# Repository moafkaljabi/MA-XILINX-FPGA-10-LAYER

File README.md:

# MA-XILINX

                                Front

                                Back

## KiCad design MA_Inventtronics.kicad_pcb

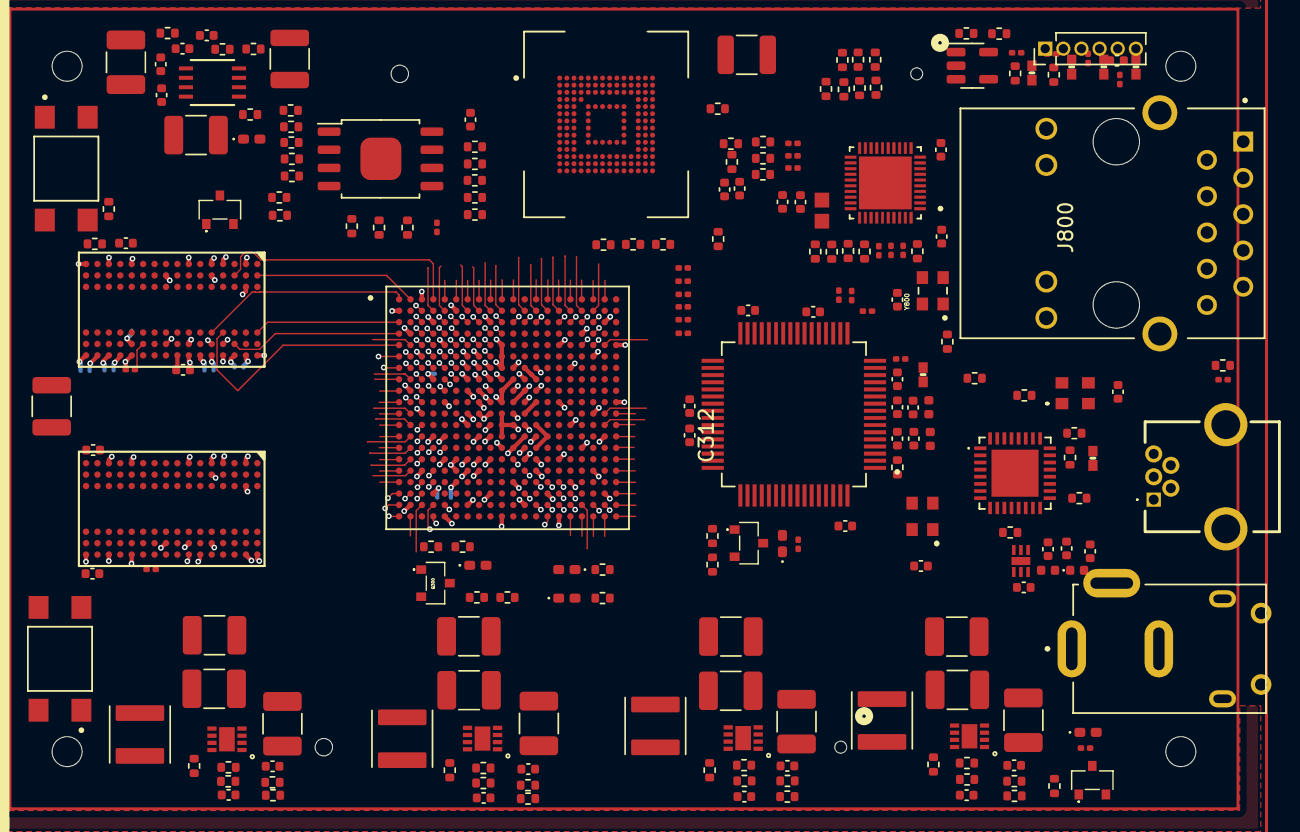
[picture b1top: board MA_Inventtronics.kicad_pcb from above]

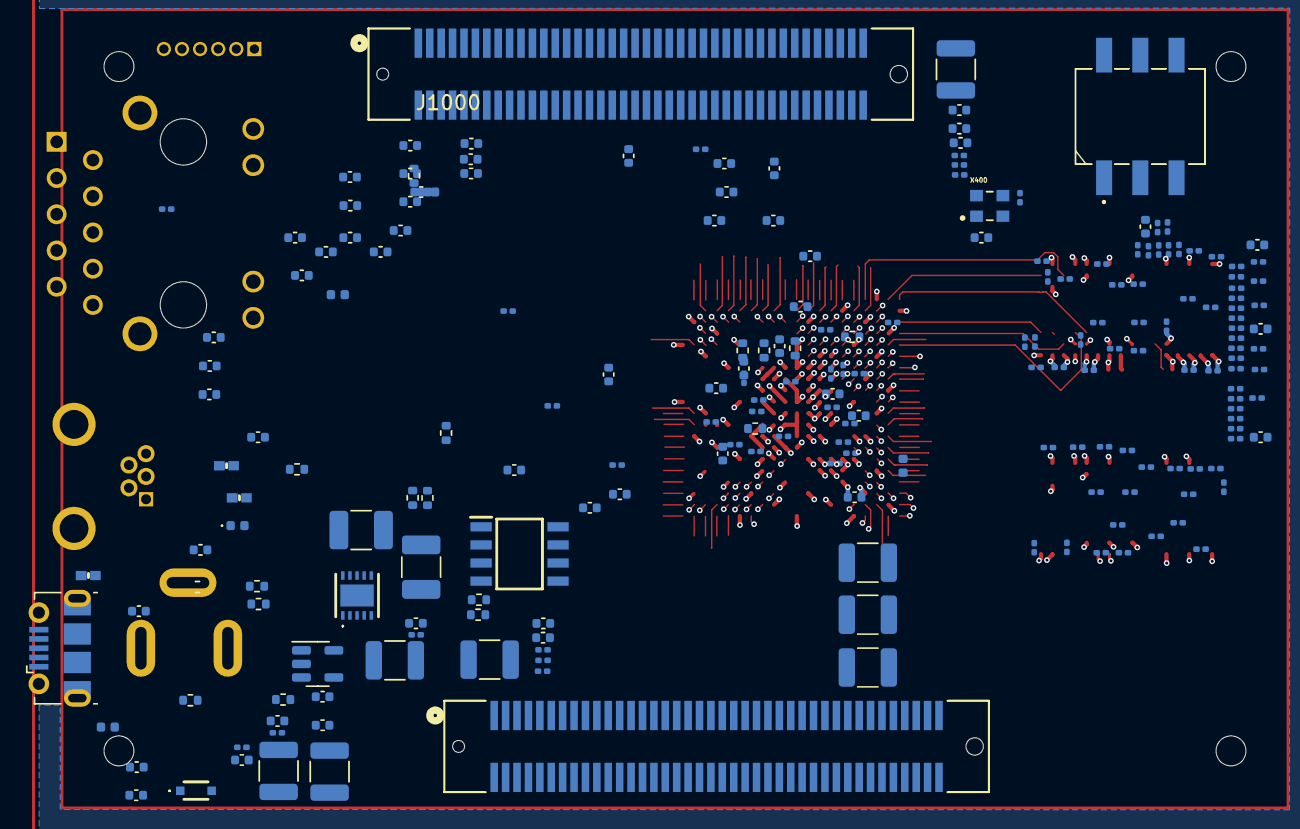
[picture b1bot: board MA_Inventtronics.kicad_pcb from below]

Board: 10 copper layers, 429 parts (207 on the bottom side), 351 nets.

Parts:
C100, C103, C104, C107, C108, C109, C112, C113, C114, C117, C118, C119, C122, C123, C124, C127: 22u; C_1210_3225Metric_Pad1.33x2.70mm_HandSolder
C101, C102, C105, C110, C115, C120, C300, C304, C306, C307, C308, C309, C310, C311, C312, C313, C314, C316, C318, C400, C401, C402, C403, C404, C405, C406, C407, C409, C412, C801, C802, C803, C804, C805, C806, C807, C808, C810, C811, C813, C815, C817, C818, C900, C901, C902, C903, C904, C905, C906, C908: 100n; C_0402_1005Metric
C106, C111, C116, C121: 22p; C_0402_1005Metric
C125, C126, C128, C129, C201, C205, C210, C213, C216, C220, C223, C229, C232, C237, C239, C244, C246, C301, C302, C303, C305, C315, C408, C410, C411, C413, C608, C609, C610, C611, C702, C712, C724, C734, C800, C809, C812, C814, C816, C819, C907: 4u7; C_0402_1005Metric
C130: 1n; C_0201_0603Metric
C200, C204, C209, C212, C221, C224, C230, C233, C234, C235, C248: 100u; C_1210_3225Metric
C202, C203, C206, C207, C208, C211, C214, C215, C217, C218, C219, C222, C225, C226, C228, C231, C238, C240, C241, C242, C243, C245, C247, C604, C605, C606, C607, C703, C713, C725, C735: 470n; C_0201_0603Metric
C227, C236: 470n; C_0402_1005Metric
C600, C601, C602, C603, C612, C613, C700, C701, C704, C705, C706, C707, C708, C709, C710, C711, C714, C715, C716, C717, C718, C719, C720, C721, C722, C723, C726, C727, C728, C729, C730, C731, C732, C733, C736, C737, C738, C739, C740, C741, C742, C743: 47n; C_0201_0603Metric
D100: PMEG1030EJ; PMEG1030EJ115
D101: LED; LED_0402_1005Metric_Pad0.77x0.64mm_HandSolder
D300, D308, D309: LED_G; LED_0402_1005Metric_Pad0.77x0.64mm_HandSolder
D301, D302, D303, D304, D306, D307, D900, D901, D902: CG0402MLU-3.3G; VARC1005X41N
D305, D903: PMEG1030EJ; D_0402_1005Metric
D400: D400; LED_0402_1005Metric_Pad0.77x0.64mm_HandSolder
D500: GREEN; LED_0402_1005Metric_Pad0.77x0.64mm_HandSolder
FB200, FB300, FB301, FB302, FB800, FB801, FB900: 120R; L_0402_1005Metric
H901, H902, H903, H904: MountingHole; MountingHole_2.1mm
J100: Barrel_Jack_Switch; GRAVITECH_CON-SOCJ-2155
J302: USB_B_Micro; USB_Micro-B_Molex-105017-0001
J304: PinHeader_1x06_P1.27mm_Vertical
J800: HR911130A; HANRUN_HR911130A
J900: GMSB0522132EU
J1000, J1001: 10144518-082802LF; CONN_10144518_AMP
L100, L101, L102, L103: 2u2; L_Abracon_ASPI-4030S
L800: LQM18PN3R3MGHD; INDC1608X100N
Q100, Q300, Q400, Q500: T2N7002AK,LM; TBAT54CLM
R100, R104, R109, R114, R119, R126, R401: 100k; R_0402_1005Metric
R101, R103, R105, R108, R110, R113, R115, R118, R120, R123, R125: 12k; R_0402_1005Metric
R102, R300, R301, R302, R303, R304: 4k7; R_0402_1005Metric
R106, R421, R422, R423, R424, R425: 68K; R_0402_1005Metric
R107, R112, R117, R122, R322, R323, R414, R416, R501: 100K; R_0402_1005Metric
R111: 200K; R_0402_1005Metric
R116: 124K; R_0402_1005Metric
R121: 453K; R_0402_1005Metric
R124, R503, R823: 510R; R_0201_0603Metric
R127, R311, R313, R315, R500, R803, R805, R806, R813, R814: 1K; R_0402_1005Metric
R128: DNP_1M; R_0402_1005Metric
R305, R306, R307, R308, R329, R330, R331, R332, R333, R334, R335, R406, R407, R408, R409, R410, R411, R419, R420, R427, R807, R811, R812, R815, R816, R817: 22R; R_0201_0603Metric
R309, R336, R337, R412, R822: 510R; R_0402_1005Metric
R310, R312, R314, R316, R318, R319, R321, R338, R404, R405: 20K; R_0402_1005Metric
R317, R320, R428: DNP_0R; R_0402_1005Metric
R324, R326, R327, R328, R400, R402, R403, R413, R417, R418, R426, R502, R903: 12K; R_0402_1005Metric
R325, R821: 2K49; R_0402_1005Metric
R600, R626, R627: 100R; R_0201_0603Metric
R601, R602, R603, R604, R605, R606, R607, R608, R609, R610, R611, R612, R613, R614, R615, R616, R617, R618, R619, R620, R621, R622, R623, R624: 49R9; R_0201_0603Metric
R625, R800, R801, R804, R818, R819, R820, R904, R905: 4K7; R_0402_1005Metric
R700, R701: 240R; R_0201_0603Metric
R802: DNP_4K7; R_0402_1005Metric
R808, R809, R810, R901: 22R; R_0402_1005Metric
R900: 1k; R_0402_1005Metric
R902: 8K06; R_0402_1005Metric
SW300, SW400: TL3305BF160QG; SW_TL3305BF160QG
SW301: 219-3LPST; 2193LPST
U100: LS1205EVD33
U101, U102, U103, U104: SY8003ADFC; SON50P200X200X65-9N
U105: BD3539FVM-TR; MSOP8_ROM
U200: XC7Z007S-1CLG400C; BGA400C80P20X20_1700X1700X160N
U300: FT2232HL-REEL; QFP50P1200X1200X160-64N
U301: 93LC56B-I_SN; SOIC127P600X175-8N
U400, U401: SN74LVC1G14DBV; SOT-23-5
U403: S40FC004C1B1I00000; BGA153N50P14X14_1150X1300X80
U404: W25Q128JVEIQ; SOIC-8_5.23x5.23mm_P1.27mm
U700, U701: MT41K256M16TW-107_P; TFBGA-96
U800: RTL8211F-CG; QFN40P500X500X90-41N
U900: USB3320C-EZK-TR; QFN50P500X500X100-33N330X330
U901: MIC2099-1YMT-TR; TMLF-6_MT_MCH
X300: ECS-2520MV-120-BN-TR; ECS2520MV120BNTR
X400: ECS-2520MV-333.3-BN-TR; OSC_ECS-2520S25-250-FN-TR
Y800: ECS-2520MV-250-BN-TR; OSC_ECS-2520S25-250-FN-TR
Y900: ECS-2520MV-130-BN-TR; ECS2520MV130BNTR

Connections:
+5V: C104.1, C109.1, C114.1, C119.1, R103.1, R105.1, R108.1, R113.1, R118.1, U101.3 (IN), U102.3 (IN), U103.3 (IN), U104.3 (IN)
/1. Power/DDR_VTT_EN: C125.1, R125.2, R126.1, R127.2, U105.2 (EN), U105.5 (VDDQ)
/1. Power/EN_1V0: R105.2, R110.2, R115.2, R120.2, U101.7 (EN), U102.7 (EN), U103.7 (EN), U104.7 (EN)
/1. Power/FB 1V0: C106.2, C111.2, C116.2, C121.2, R106.2, R107.1, R111.2, R112.1, R116.2, R117.1, R121.2, R122.1, U101.1 (FB), U102.1 (FB), U103.1 (FB), U104.1 (FB)
/1. Power/LED_PWR_A: D101.2 (A), R124.2
/1. Power/LED_PWR_C: D101.1 (K), Q100.2 (S)
/1. Power/PG_1V0: C105.1, C110.1, C115.1, C120.1, R103.2, R104.1, R108.2, R109.1, R113.2, R114.1, R118.2, R119.1, R123.2, U101.2 (PG), U102.2 (PG), U103.2 (PG), U104.2 (PG)
/1. Power/PWR_EN: C101.1, R100.2, U100.7 (EN)
/1. Power/SW_1V0: L100.1, L101.1, L102.1, L103.1, U101.6 (LX), U102.6 (LX), U103.6 (LX), U104.6 (LX)
/1. Power/eFuse_ILIM: R102.1, U100.5 (ILIM)
/1. Power/eFuse_SS: C102.1, U100.6 (SS)
/1. Power/eFuse_VCP: R101.1, U100.4 (VCP)
/3. Zynq Config, JTAG, Debug/CLK 12 MHZ: R338.1, X300.3 (OUT)
/3. Zynq Config, JTAG, Debug/DONE: Q300.1 (G), R302.2, U200.R11 (DONE_0)
/3. Zynq Config, JTAG, Debug/FTDI EECLK: R326.1, U300.62 (EECLK), U301.2 (CLK)
/3. Zynq Config, JTAG, Debug/FTDI EECS: R327.1, U300.63 (EECS), U301.1 (CS)
/3. Zynq Config, JTAG, Debug/FTDI EEDAT: R325.2, U300.61 (EEDATA), U301.3 (DI)
/3. Zynq Config, JTAG, Debug/FTDI NRST: R322.1, R323.2, U300.14 (~RESET)
/3. Zynq Config, JTAG, Debug/FTDI OSCI: R338.2, U300.2 (OSCI)
/3. Zynq Config, JTAG, Debug/FTDI REF: R328.2, U300.6 (REF)
/3. Zynq Config, JTAG, Debug/FTDI RX: R335.2, U300.39 (BDBUS1)
/3. Zynq Config, JTAG, Debug/FTDI TCK: R329.1, U300.16 (ADBUS0)
/3. Zynq Config, JTAG, Debug/FTDI TDI: R330.1, U300.17 (ADBUS1)
/3. Zynq Config, JTAG, Debug/FTDI TDO: R331.1, U300.18 (ADBUS2)
/3. Zynq Config, JTAG, Debug/FTDI TMS: R332.1, U300.19 (ADBUS3)
/3. Zynq Config, JTAG, Debug/FTDI TX: R334.2, U300.38 (BDBUS0)
/3. Zynq Config, JTAG, Debug/FTDI VPHY: C305.1, C306.1, FB302.2, U300.4 (VPHY)
/3. Zynq Config, JTAG, Debug/FTDI VPLL: C303.1, C304.1, FB301.2, U300.9 (VPLL)
/3. Zynq Config, JTAG, Debug/FTDI_RX_LED_A: D308.2 (A), R336.2
/3. Zynq Config, JTAG, Debug/FTDI_RX_LED_K: D308.1 (K), U300.54 (BCBUS3)
/3. Zynq Config, JTAG, Debug/FTDI_TX_LED_A: D309.2 (A), R337.2
/3. Zynq Config, JTAG, Debug/FTDI_TX_LED_K: D309.1 (K), U300.55 (BCBUS4)
/3. Zynq Config, JTAG, Debug/LED_DONE_A: D300.2 (A), R309.2
/3. Zynq Config, JTAG, Debug/LED_DONE_C: D300.1 (K), Q300.3 (D)
/3. Zynq Config, JTAG, Debug/M0: R310.1, R315.1, SW301.1
/3. Zynq Config, JTAG, Debug/M1: R312.1, R313.1, SW301.2
/3. Zynq Config, JTAG, Debug/M2: R311.1, R314.2, SW301.3
/3. Zynq Config, JTAG, Debug/M3: R316.2, R317.2, R318.1
/3. Zynq Config, JTAG, Debug/M4: R319.2, R320.2, R321.1
/3. Zynq Config, JTAG, Debug/NINIT: R303.2, U200.R10 (INIT_B_0)
/3. Zynq Config, JTAG, Debug/NPROGARAM: R304.2, SW300.3, SW300.4, U200.L6 (PROGRAM_B_0)
/3. Zynq Config, JTAG, Debug/USB FTDI D N: D306.2, D307.2, J302.2 (D-), U300.7 (DM)
/3. Zynq Config, JTAG, Debug/USB FTDI D P: J302.3 (D+), U300.8 (DP)
/3. Zynq Config, JTAG, Debug/VUSB FILTER: C302.1, D305.2 (A), FB300.2, R322.2
/4. Zynq Processing System (PS)/CLK 33M33: R420.1, X400.3 (OUT)
/4. Zynq Processing System (PS)/FLASH CLK M4: R419.2, U404.6 (CLK)
/5. Zynq Programmable Logic (PL)/LED PL: R501.1, R502.1, U200.T12 (IO_L2P_T0_34)
/5. Zynq Programmable Logic (PL)/NPUDC: R500.2, U200.U13 (IO_L3P_T0_DQS_PUDC_B_34)
/6. Zynq DDR Interface & Termination/DDR NRST: R625.2, U200.B4 (PS_DDR_DRST_B_502)
/7. 1GB DDR3L Modules/DDR ZQ1: R700.1, U700.L8 (ZQ)
/7. 1GB DDR3L Modules/DDR ZQ2: R701.1, U701.L8 (ZQ)
/8. Gigabit Ethernet/CLK 25MHZ: R815.1, Y800.3 (OUT)
/8. Gigabit Ethernet/ETH CLK 25MHZ: R815.2, U800.37 (XTAL_OUT/EXT_CLK)
/8. Gigabit Ethernet/ETH PHY RXCLK: R812.2, U800.27 (RXC/PHYAD1)
/8. Gigabit Ethernet/ETH PHY RXCTL: R811.2, U800.26 (RXCTL/PHYAD2)
/8. Gigabit Ethernet/ETH PHY RXD0: J800.2, J800.4, J800.5, J800.8, R807.2, U800.1 (MDIP0), U800.4 (MDIP1), U800.6 (MDIP2), U800.9 (MDIP3), U800.25 (RXD0/RXDLY)
/8. Gigabit Ethernet/ETH PHY RXD1: J800.3, J800.6, J800.7, J800.9, R808.2, U800.2 (MDIN0), U800.5 (MDIN1), U800.7 (MDIN2), U800.10 (MDIN3), U800.24 (RXD1/TXDLY)
/8. Gigabit Ethernet/ETH PHY RXD2: R809.2, U800.23 (RXD2/PLLOFF)
/8. Gigabit Ethernet/ETH PHY RXD3: R810.2, U800.22 (RXD3/PHYAD0)
/8. Gigabit Ethernet/ETH REG OUT: L800.1, U800.30 (REG_OUT)
/8. Gigabit Ethernet/ETH RSET: R821.2, U800.39 (RSET)
/8. Gigabit Ethernet/ETH XTAL IN: R816.1, U800.36 (XTAL_IN)
/8. Gigabit Ethernet/ETH XTALOUT: R817.1, U800.35 (CLKOUT)
/9. USB 2.0 High-Speed (OTG)/CLK 13MHZ: R901.1, Y900.3 (OUT)
/9. USB 2.0 High-Speed (OTG)/USB HS D N: D900.2, J900.2 (D-), U900.19 (DM)
/9. USB 2.0 High-Speed (OTG)/USB HS D P: D901.2, J900.3 (D+), U900.18 (DP)
/9. USB 2.0 High-Speed (OTG)/USB HS ID: D902.2, J900.4 (ID), U900.23 (ID)
/9. USB 2.0 High-Speed (OTG)/USB HS VBUS FILT: C905.1, D903.1 (K), FB900.1, R903.2
/9. USB 2.0 High-Speed (OTG)/USB ILM: R905.1, U901.2 (ILIMIT)
/9. USB 2.0 High-Speed (OTG)/USB PHY RBIAS: R902.1, U900.24 (RBIAS)
/9. USB 2.0 High-Speed (OTG)/USB PHY VBUS: R903.1, U900.22 (VBUS)
/9. USB 2.0 High-Speed (OTG)/USB REFCLK 13MHZ: R901.2, U900.26 (REFCLK)
DDR A0: R609.1, U200.N2 (PS_DDR_A0_502), U700.N3 (A0), U701.N3 (A0)
DDR A1: R610.1, U200.K2 (PS_DDR_A1_502), U700.P7 (A1), U701.P7 (A1)
DDR A2: R611.1, U200.M3 (PS_DDR_A2_502), U700.P3 (A2), U701.P3 (A2)
DDR A3: R612.1, U200.K3 (PS_DDR_A3_502), U700.N2 (A3), U701.N2 (A3)
DDR A4: R613.1, U200.M4 (PS_DDR_A4_502), U700.P8 (A4), U701.P8 (A4)
DDR A5: R614.1, U200.L1 (PS_DDR_A5_502), U700.P2 (A5), U701.P2 (A5)
DDR A6: R615.1, U200.L4 (PS_DDR_A6_502), U700.R8 (A6), U701.R8 (A6)
DDR A7: R616.1, U200.K4 (PS_DDR_A7_502), U700.R2 (A7), U701.R2 (A7)
DDR A8: R617.1, U200.K1 (PS_DDR_A8_502), U700.T8 (A8), U701.T8 (A8)
DDR A9: R618.1, U200.J4 (PS_DDR_A9_502), U700.R3 (A9), U701.R3 (A9)
DDR A10: R619.1, U200.F5 (PS_DDR_A10_502), U700.L7 (A10/AP), U701.L7 (A10/AP)
DDR A11: R620.1, U200.G4 (PS_DDR_A11_502), U700.R7 (A11), U701.R7 (A11)
DDR A12: R621.1, U200.E4 (PS_DDR_A12_502), U700.N7 (A12/BC#), U701.N7 (A12/BC#)
DDR A13: R622.1, U200.D4 (PS_DDR_A13_502), U700.T3 (A13), U701.T3 (A13)
DDR A14: R623.1, U200.F4 (PS_DDR_A14_502), U700.T7 (A14), U701.T7 (A14)
DDR BA0: R606.1, U200.L5 (PS_DDR_BA0_502), U700.M2 (BA0), U701.M2 (BA0)
DDR BA1: R607.1, U200.R4 (PS_DDR_BA1_502), U700.N8 (BA1), U701.N8 (BA1)
DDR BA2: R608.1, U200.J5 (PS_DDR_BA2_502), U700.M3 (BA2), U701.M3 (BA2)
DDR CK N: R600.1, U200.M2 (PS_DDR_CKN_502), U700.K7 (CLKN), U701.K7 (CLKN)
DDR CK P: R600.2, U200.L2 (PS_DDR_CKP_502), U700.J7 (CLKP), U701.J7 (CLKP)
DDR CKE: R601.1, U200.N3 (PS_DDR_CKE_502), U700.K9 (CKE), U701.K9 (CKE)
DDR DM0: U200.A1 (PS_DDR_DM0_502), U700.E7 (DML)
DDR DM1: U200.F1 (PS_DDR_DM1_502), U700.D3 (DMU)
DDR DM2: U200.T1 (PS_DDR_DM2_502), U701.E7 (DML)
DDR DM3: U200.Y1 (PS_DDR_DM3_502), U701.D3 (DMU)
DDR DQ0: U200.C3 (PS_DDR_DQ0_502), U700.A3 (DQU7)
DDR DQ1: U200.B3 (PS_DDR_DQ1_502), U700.C3 (DQU1)
DDR DQ2: U200.A4 (PS_DDR_DQ3_502), U700.C2 (DQU3)
DDR DQ3: U200.A2 (PS_DDR_DQ2_502), U700.A2 (DQU5)
DDR DQ4: U200.D3 (PS_DDR_DQ4_502), U700.B8 (DQU6)
DDR DQ5: U200.E1 (PS_DDR_DQ7_502), U700.D7 (DQU0)
DDR DQ6: U200.C1 (PS_DDR_DQ6_502), U700.A7 (DQU4)
DDR DQ7: U200.D1 (PS_DDR_DQ5_502), U700.C8 (DQU2)
DDR DQ8: U200.E2 (PS_DDR_DQ8_502), U700.H3 (DQL4)
DDR DQ9: U200.E3 (PS_DDR_DQ9_502), U700.E3 (DQL0)
DDR DQ10: U200.G3 (PS_DDR_DQ10_502), U700.G2 (DQL6)
DDR DQ11: U200.H3 (PS_DDR_DQ11_502), U700.H7 (DQL7)
DDR DQ12: U200.J3 (PS_DDR_DQ12_502), U700.F7 (DQL1)
DDR DQ13: U200.H2 (PS_DDR_DQ13_502), U700.H8 (DQL5)
DDR DQ14: U200.H1 (PS_DDR_DQ14_502), U700.F2 (DQL2)
DDR DQ15: U200.J1 (PS_DDR_DQ15_502), U700.F8 (DQL3)
DDR DQ16: U200.P1 (PS_DDR_DQ16_502), U701.E3 (DQL0)
DDR DQ17: U200.P3 (PS_DDR_DQ17_502), U701.H3 (DQL4)
DDR DQ18: U200.R3 (PS_DDR_DQ18_502), U701.G2 (DQL6)
DDR DQ19: U200.R1 (PS_DDR_DQ19_502), U701.F2 (DQL2)
DDR DQ20: U200.T4 (PS_DDR_DQ20_502), U701.F7 (DQL1)
DDR DQ21: U200.U4 (PS_DDR_DQ21_502), U701.F8 (DQL3)
DDR DQ22: U200.U2 (PS_DDR_DQ22_502), U701.H8 (DQL5)
DDR DQ23: U200.U3 (PS_DDR_DQ23_502), U701.H7 (DQL7)
DDR DQ24: U200.V1 (PS_DDR_DQ24_502), U701.A2 (DQU5)
DDR DQ25: U200.Y3 (PS_DDR_DQ25_502), U701.C8 (DQU2)
DDR DQ26: U200.W1 (PS_DDR_DQ26_502), U701.A3 (DQU7)
DDR DQ27: U200.Y4 (PS_DDR_DQ27_502), U701.B8 (DQU6)
DDR DQ28: U200.Y2 (PS_DDR_DQ28_502), U701.C3 (DQU1)
DDR DQ29: U200.W3 (PS_DDR_DQ29_502), U701.D7 (DQU0)
DDR DQ30: U200.V2 (PS_DDR_DQ30_502), U701.C2 (DQU3)
DDR DQ31: U200.V3 (PS_DDR_DQ31_502), U701.A7 (DQU4)
DDR DQS0 N: U200.B2 (PS_DDR_DQS_N0_502), U700.B7 (DQSUN)
DDR DQS0 P: U200.C2 (PS_DDR_DQS_P0_502), U700.C7 (DQSUP)
DDR DQS1 N: U200.F2 (PS_DDR_DQS_N1_502), U700.G3 (DQSLN)
DDR DQS1 P: U200.G2 (PS_DDR_DQS_P1_502), U700.F3 (DQSLP)
DDR DQS2 N: U200.T2 (PS_DDR_DQS_N2_502), U701.G3 (DQSLN)
DDR DQS2 P: U200.R2 (PS_DDR_DQS_P2_502), U701.F3 (DQSLP)
DDR DQS3 N: U200.W4 (PS_DDR_DQS_N3_502), U701.B7 (DQSUN)
DDR DQS3 P: U200.W5 (PS_DDR_DQS_P3_502), U701.C7 (DQSUP)
DDR NCAS: R604.1, U200.P5 (PS_DDR_CAS_B_502), U700.K3 (CAS#), U701.K3 (CAS#)
DDR NCS: R602.1, U200.N1 (PS_DDR_CS_B_502), U700.L2 (CS#), U701.L2 (CS#)
DDR NRAS: R603.1, R605.1, U200.M5 (PS_DDR_WE_B_502), U200.P4 (PS_DDR_RAS_B_502), U700.J3 (RAS#), U700.L3 (WE#), U701.J3 (RAS#), U701.L3 (WE#)
DDR NRST: U700.T2 (RESET#), U701.T2 (RESET#)
DDR ODT: R624.1, U200.N5 (PS_DDR_ODT_502), U700.K1 (ODT), U701.K1 (ODT)
ETH MDC: U200.C10 (PS_MIO17_501), U800.13 (MDC)
ETH MDIO: R814.1, U200.C11 (PS_MIO15_500), U800.14 (MDIO)
ETH NINT: R813.1, U200.E12 (PS_MIO38_501), U800.31 (INTB/PMEB)
ETH NRST: R416.1, U200.C17 (PS_MIO40_501), U401.2, U800.12 (PHYRSTB)
ETH NRST +3V3: R417.2, U401.4
ETH PHY TXCLK: R406.2, U800.20 (TXC)
ETH PHY TXCTL: R411.2, U800.19 (TXCTL)
ETH PHY TXD0: R407.2, U800.18 (TXD0)
ETH PHY TXD1: R408.2, U800.17 (TXD1)
ETH PHY TXD2: R409.2, U800.16 (TXD2)
ETH PHY TXD3: R410.2, U800.15 (TXD3)
ETH RXCLK: R806.2, R812.1, U200.B17 (PS_MIO37_501)
ETH RXCTL: R805.2, R811.1, U200.D13 (PS_MIO28_501)
ETH RXD0: R800.1, R807.1, U200.D11 (PS_MIO36_501)
ETH RXD1: R801.1, R808.1, U200.A16 (PS_MIO34_501)
ETH RXD2: R802.1, R803.2, R809.1, U200.F15 (PS_MIO32_501)
ETH RXD3: R804.1, R810.1, U200.A15 (PS_MIO30_501)
Earth: C100.2, C101.2, C102.2, C103.2, C104.2, C105.2, C107.2, C108.2, C109.2, C110.2, C112.2, C113.2, C114.2, C115.2, C117.2, C118.2, C119.2, C120.2, C122.2, C123.2, C124.2, C125.2, C126.2, C127.2, C128.2, C129.2, C130.2, J100.2, J100.3, Q100.3 (D), R102.2, R104.2, R107.2, R109.2, R110.1, R112.2, R114.2, R115.1, R117.2, R119.2, R120.1, R122.2, R126.2, R128.2, U100.11 (GND), U101.8 (SGND), U102.8 (SGND), U103.8 (SGND), U104.8 (SGND), U105.1 (GND)
GNDPWR: C130.1, J302.6 (Shield), J800.S1 (SHIELD), J800.S2 (SHIELD), J900.SH, R128.1
GNDREF: C200.2, C201.2, C202.2, C203.2, C204.2, C205.2, C206.2, C207.2, C208.2, C209.2, C210.2, C211.2, C212.2, C213.2, C214.2, C215.2, C216.2, C217.2, C218.2, C219.2, C220.2, C221.2, C222.2, C223.2, C224.2, C225.2, C226.2, C227.2, C228.2, C229.2, C230.2, C231.2, C232.2, C233.2, C234.2, C235.2, C236.2, C237.2, C238.2, C239.2, C240.2, C241.2, C242.1, C243.1, C244.1, C245.1, C246.1, C247.1, C248.1, C300.2, C301.2, C302.2, C303.2, C304.2, C305.2, C306.2, C307.2, C308.2, C309.2, C310.2, C311.2, C312.2, C313.2, C314.2, C315.2, C316.2, C318.2, C400.2, C401.2, C402.2, C403.2, C404.2, C405.2, C406.2, C407.2, C408.2, C409.2, C410.2, C411.2, C412.2, C413.2, C600.2, C601.2, C602.2, C603.2, C604.2, C605.2, C606.2, C607.2, C608.2, C609.2, C610.2, C611.2, C612.2, C613.2, C701.2, C702.2, C703.2, C704.2, C705.2, C706.2, C707.2, C708.2, C709.2, C710.2, C711.2, C712.2, C713.2, C714.2, C715.2, C716.2, C717.2, C718.2, C719.2, C720.2, C721.2, C723.2, C724.2, C725.2, C726.2, C727.2, C728.2, C729.2, C730.2, C731.2, C732.2, C733.2, C734.2, C735.2, C736.2, C737.2, C738.2, C739.2, C740.2, C741.2, C742.2, C743.2, C800.2, C801.2, C802.2, C803.2, C804.2, C805.2, C806.2, C807.2, C808.2, C809.2, C810.2, C811.2, C812.2, C813.2, C814.2, C815.2, C816.2, C817.2, C818.2, C819.2, C900.2, C901.2, C902.2, C903.2, C904.2, C905.2, C906.2, C907.2, C908.2, D301.1, D302.1, D303.1, D304.1, D306.1, D307.1, D900.1, D901.1, D902.1, J302.5 (GND), J304.5 (GND), J800.10 (GND), J900.5 (GND), J1000.1, J1000.2, J1000.7, J1000.8, J1000.13, J1000.14, J1000.19, J1000.20, J1000.26, J1000.31, J1000.32, J1000.38, J1000.43, J1000.44, J1000.49, J1000.50, J1000.55, J1000.56, J1000.61, J1000.62, J1000.67, J1000.68, J1000.69, J1000.70, J1000.71, J1000.72, J1000.73, J1000.74, J1000.77, J1000.78, J1000.79, J1000.80, J1001.1, J1001.2, J1001.13, J1001.14, J1001.19, J1001.20, J1001.22, J1001.24, J1001.25, J1001.26, J1001.28, J1001.30, J1001.31, J1001.32, J1001.34, J1001.36, J1001.37, J1001.38, J1001.43, J1001.44, J1001.49, J1001.55, J1001.56, J1001.58, J1001.60, J1001.61, J1001.62, J1001.64, J1001.66, J1001.67, J1001.68, J1001.73, J1001.79, J1001.80, Q300.2 (S), Q400.2 (S), Q500.2 (S), R311.2, R313.2, R315.2, R318.2, R321.2, R323.1, R328.1, R401.2, R404.2, R414.2, R416.2, R501.2, R625.1, R627.1, R700.2, R701.2, R803.1, R805.1, R806.1, R816.2, R819.2, R821.1, R902.2, R904.2, R905.2, SW300.1, SW300.2, SW400.1, SW400.2, U200.A8 (GND), U200.A18 (GND), U200.B1 (GND), U200.B11 (GND), U200.C4 (GND), U200.C9 (GND), U200.C14 (GND), U200.D17 (GND), U200.E10 (GND), U200.E20 (GND), U200.F3 (GND), U200.F7 (GND), U200.F10 (RSVDGND), U200.G10 (GND), U200.G12 (GND), U200.G16 (GND), U200.H7 (GND), U200.H9 (GND), U200.H11 (GND), U200.H13 (GND), U200.H19 (GND), U200.J2 (GND), U200.J8 (GND), U200.J10 (GNDADC_0), U200.J12 (GND), U200.K5 (GND), U200.K7 (GND), U200.K9 (VP_0), U200.K10 (VREFN_0), U200.K11 (GND), U200.K13 (GND), U200.K15 (GND), U200.L8 (GND), U200.L9 (VREFP_0), U200.L10 (VN_0), U200.L12 (GND), U200.L18 (GND), U200.M1 (GND), U200.M7 (GND), U200.M9 (DXP_0), U200.M10 (DXN_0), U200.M11 (GND), U200.M13 (GND), U200.N4 (GND), U200.N8 (GND), U200.N10 (GND), U200.N12 (GND), U200.N14 (GND), U200.P7 (GND), U200.P9 (GND), U200.P11 (GND), U200.P13 (GND), U200.P17 (GND), U200.R8 (GND), U200.R12 (GND), U200.R20 (GND), U200.T3 (GND), U200.T7 (GND), U200.T13 (GND), U200.U6 (GND), U200.U16 (GND), U200.V9 (GND), U200.V19 (GND), U200.W2 (GND), U200.W12 (GND), U200.Y5 (GND), U200.Y15 (GND), U300.1 (GND), U300.5 (GND), U300.10 (AGND), U300.11 (GND), U300.13 (TEST), U300.15 (GND), U300.25 (GND), U300.35 (GND), U300.47 (GND), U300.51 (GND), U301.5 (VSS), U400.3 (GND), U401.3 (GND), U403.A6 (VSS), U403.C4 (VSSQ), U403.E7 (VSS), U403.G5 (VSS), U403.H10 (VSS), U403.J5 (VSS), U403.K8 (VSS), U403.N2 (VSSQ), U403.N5 (VSSQ), U403.P4 (VSSQ), U403.P6 (VSSQ), U404.4 (GND), U404.9 (EP), U700.A9 (VSS1), U700.B1 (VSSQ1), U700.B3 (VSS2), U700.B9 (VSSQ2), U700.D1 (VSSQ3), U700.D8 (VSSQ4), U700.E1 (VSS3), U700.E2 (VSSQ5), U700.E8 (VSSQ6), U700.F9 (VSSQ7), U700.G1 (VSSQ8), U700.G8 (VSS4), U700.G9 (VSSQ9), U700.J2 (VSS5), U700.J8 (VSS6), U700.M1 (VSS7), U700.M9 (VSS8), U700.P1 (VSS9), U700.P9 (VSS10), U700.T1 (VSS11), U700.T9 (VSS12), U701.A9 (VSS1), U701.B1 (VSSQ1), U701.B3 (VSS2), U701.B9 (VSSQ2), U701.D1 (VSSQ3), U701.D8 (VSSQ4), U701.E1 (VSS3), U701.E2 (VSSQ5), U701.E8 (VSSQ6), U701.F9 (VSSQ7), U701.G1 (VSSQ8), U701.G8 (VSS4), U701.G9 (VSSQ9), U701.J2 (VSS5), U701.J8 (VSS6), U701.M1 (VSS7), U701.M9 (VSS8), U701.P1 (VSS9), U701.P9 (VSS10), U701.T1 (VSS11), U701.T9 (VSS12), U800.41 (GND), U900.8 (REFSEL0), U900.11 (REFSEL1), U900.33 (GND), U901.5 (GND), U901.7 (EP), X300.2 (GND), X400.2 (GND), Y800.2 (GND), Y900.2 (GND)
MIO49: J1000.65, U200.C12 (PS_MIO23_501)
MIO50: J1000.76, U200.B13 (PS_MIO21_501)
MIO VREF 0V9: C400.1, R400.2, R401.1, U200.E11 (PS_MIO_VREF_501)
unnamed: C106.1, C107.1, C108.1, L100.2, R106.1
unnamed: C111.1, C112.1, C113.1, L101.2, R111.1
unnamed: C116.1, C117.1, C118.1, L102.2, R116.1
unnamed: C121.1, C122.1, C123.1, L103.2, R121.1
unnamed: C200.1, C201.1, C202.1, C203.1, U200.G13 (VCCINT), U200.H12 (VCCINT), U200.J13 (VCCINT), U200.K12 (VCCINT), U200.L13 (VCCINT), U200.M12 (VCCINT), U200.N13 (VCCINT), U200.P12 (VCCINT), U200.R13 (VCCINT)
unnamed: C204.1, C205.1, C206.1, C207.1, C208.1, U200.G7 (VCCPINT), U200.J7 (VCCPINT), U200.L7 (VCCPINT), U200.N7 (VCCPINT), U200.P8 (VCCPINT), U200.R7 (VCCPINT)
unnamed: C212.1, C213.1, C214.1, U200.A13 (VCCO_MIO1_501), U200.B16 (VCCO_MIO1_501), U200.D12 (VCCO_MIO1_501), U200.E15 (VCCO_MIO1_501)
unnamed: C209.1, C210.1, C211.1, U200.B6 (VCCO_MIO0_500), U200.D7 (VCCO_MIO0_500)
unnamed: C222.1, C223.1, C224.1, U200.F8 (VCCPAUX), U200.G9 (VCCPAUX), U200.H8 (VCCPAUX), U200.K8 (VCCPAUX), U200.M8 (VCCPAUX)
unnamed: C219.1, C220.1, C221.1, U200.J11 (VCCAUX), U200.L11 (VCCAUX), U200.N9 (VCCAUX), U200.N11 (VCCAUX), U200.P10 (VCCAUX), U200.R9 (VCCAUX)
unnamed: C225.1, C226.1, C227.1, C228.1, C229.1, C230.1, U200.A3 (VCCO_DDR_502), U200.D2 (VCCO_DDR_502), U200.E5 (VCCO_DDR_502), U200.G1 (VCCO_DDR_502), U200.H4 (VCCO_DDR_502), U200.L3 (VCCO_DDR_502), U200.P2 (VCCO_DDR_502), U200.R5 (VCCO_DDR_502), U200.U1 (VCCO_DDR_502), U200.V4 (VCCO_DDR_502)
unnamed: C231.1, C232.1, C233.1, U200.G11 (VCCBRAM), U200.H10 (VCCBRAM)
unnamed: C235.1, C236.1, C237.1, C238.1, C239.1, C240.1, C241.1, U200.N19 (VCCO_34), U200.R15 (VCCO_34), U200.T18 (VCCO_34), U200.V14 (VCCO_34), U200.W17 (VCCO_34), U200.Y20 (VCCO_34)
unnamed: C242.2, C243.2, C244.2, C245.2, C246.2, C247.2, C248.2, U200.C19 (VCCO_35), U200.F18 (VCCO_35), U200.H14 (VCCO_35), U200.J17 (VCCO_35), U200.K20 (VCCO_35), U200.M16 (VCCO_35)
unnamed: U200.T8 (VCCO_13), U200.U11 (VCCO_13), U200.W7 (VCCO_13), U200.Y10 (VCCO_13)
unnamed: SW301.4, SW301.5, SW301.6
unnamed: R336.1, R337.1
unnamed: R326.2, R327.2
unnamed: R421.1, R422.1, R423.1, R424.1, R425.1, R426.1
unnamed: C407.1, C408.1, C409.1, C410.1, C411.1, U403.C6 (VCCQ), U403.E6 (VCC), U403.F5 (VCC), U403.J10 (VCC), U403.K9 (VCC), U403.M4 (VCCQ), U403.N4 (VCCQ), U403.P3 (VCCQ), U403.P5 (VCCQ)
unnamed: C600.1, C601.1, C602.1, C603.1, C604.1, C605.1, C606.1, C607.1, C608.1, C609.1, C610.1, C611.1, R601.2, R602.2, R603.2, R604.2, R605.2, R606.2, R607.2, R608.2, R609.2, R610.2, R611.2, R612.2, R613.2, R614.2, R615.2, R616.2, R617.2, R618.2, R619.2, R620.2, R621.2, R622.2, R623.2, R624.2
unnamed: R800.2, R801.2, R802.2, R804.2
unnamed: R813.2, R814.2
unnamed: J800.11, J800.14
unnamed: R818.1, R820.1
unnamed: C804.1, C805.1, C806.1, U800.3 (AVDD10), U800.8 (AVDD10), U800.38 (AVDD10)
unnamed: C809.1, C810.1, L800.2
unnamed: C807.1, C808.1, C816.1, C817.1, FB801.1, U800.11 (AVDD33), U800.40 (AVDD33)
unnamed: C818.1, C819.1, FB801.2
unnamed: J1000.3, J1000.5, J1000.9, J1000.11, J1000.15, J1000.17
unnamed: J1001.46, J1001.48, J1001.50, J1001.52, J1001.54
unnamed: J1001.3, J1001.5, J1001.7, J1001.9, J1001.11
unnamed: J1001.4, J1001.6, J1001.8, J1001.10, J1001.12
unnamed: J1001.70, J1001.72, J1001.74, J1001.76, J1001.78
unnamed: J1000.4, J1000.6, J1000.10, J1000.12, J1000.16, J1000.18
unnamed: C812.1, C813.1, FB800.1
unnamed: D100.2 (A), J100.1
unnamed: C100.1, D100.1 (K)
unnamed: D400.2 (A), R412.2
unnamed: D400.1 (K), Q400.3 (D)
unnamed: D500.2 (A), R503.2
unnamed: D500.1 (K), Q500.3 (D)
unnamed: C908.1, D903.2 (A), U901.1 (VOUT)
unnamed: C301.1, FB300.1, J302.1 (VBUS)
unnamed: D303.2, J304.4 (TCK), R307.2
unnamed: D301.2, J304.2 (TDI), R305.2
unnamed: D302.2, J304.3 (TDO), R306.2
unnamed: D304.2, J304.1 (TMS), R308.2
unnamed: C300.1, J304.6 (VDD), R300.1, R301.1, R302.1, R303.1, R304.1
unnamed: J800.12, R822.1
unnamed: J800.13, R823.1
unnamed: C906.1, FB900.2, J900.1 (VCC)
unnamed: Q100.1 (G), R123.1
unnamed: Q400.1 (G), R413.2
unnamed: Q500.1 (G), R502.2
unnamed: R100.1, U100.1 (IN_1), U100.2 (IN_2), U100.3 (IN_3)
unnamed: C103.1, U100.8 (OUT_1), U100.9 (OUT_2), U100.10 (OUT_3)
unnamed: C126.1, U105.6 (VCC)
unnamed: C129.1, U105.4 (VREF)
unnamed: C127.1, C128.1, U105.3 (VTTS), U105.8 (VTT)
unnamed: C124.1, U105.7 (VTT_IN)
unnamed: C612.1, C613.1, U200.H6 (PS_DDR_VREF0_502), U200.P6 (PS_DDR_VREF1_502)
unnamed: R626.1, U200.G5 (PS_DDR_VRN_502)
unnamed: R627.2, U200.H5 (PS_DDR_VRP_502)
unnamed: R411.1, U200.F14 (PS_MIO39_501)
unnamed: R410.1, U200.A17 (PS_MIO41_501)
unnamed: R409.1, U200.D10 (PS_MIO43_501)
unnamed: R408.1, U200.B18 (PS_MIO45_501)
unnamed: R407.1, U200.E14 (PS_MIO47_501)
unnamed: R406.1, U200.A19 (PS_MIO49_501)
unnamed: C218.1, U200.J9 (VCCADC_0)
unnamed: C217.1, U200.F11 (VCCBATT_0)
unnamed: C215.1, C216.1, FB200.1, U200.G8 (VCCPLL)
unnamed: U200.N6 (RSVDVCC3), U200.R6 (RSVDVCC2), U200.T6 (RSVDVCC1)
unnamed: C234.1, U200.K6 (VCCO_0)
unnamed: R333.1, U300.22 (ADBUS5)
unnamed: C310.1, C311.1, C312.1, C313.1, U300.20 (VCCIO-1), U300.31 (VCCIO-2), U300.42 (VCCIO-3), U300.56 (VCCIO-4)
unnamed: C307.1, C308.1, C309.1, U300.12 (VCORE-1), U300.37 (VCORE-2), U300.64 (VCORE-3)
unnamed: C314.1, U300.50 (VREGIN)
unnamed: C315.1, U300.49 (VREGOUT)
unnamed: R324.1, R325.1, U301.4 (DO)
unnamed: C316.1, U301.8 (VCC)
unnamed: C403.1, U400.5 (VCC)
unnamed: C404.1, U401.5 (VCC)
unnamed: R427.2, U403.M6 (CLK)
unnamed: C412.1, C413.1, U403.C2 (VDDI)
unnamed: R426.2, R428.2, U403.K5 (~RST)
unnamed: C405.1, U404.8 (VCC)
unnamed: C702.1, C703.1, C704.1, C705.1, C706.1, C707.1, C708.1, C709.1, C710.1, C711.1, U700.B2 (VDD1), U700.D9 (VDD2), U700.G7 (VDD3), U700.K2 (VDD4), U700.K8 (VDD5), U700.N1 (VDD6), U700.N9 (VDD7), U700.R1 (VDD8), U700.R9 (VDD9)
unnamed: C712.1, C713.1, C714.1, C715.1, C716.1, C717.1, C718.1, C719.1, C720.1, C721.1, U700.A1 (VDDQ1), U700.A8 (VDDQ2), U700.C1 (VDDQ3), U700.C9 (VDDQ4), U700.D2 (VDDQ5), U700.E9 (VDDQ6), U700.F1 (VDDQ7), U700.H2 (VDDQ8), U700.H9 (VDDQ9)
unnamed: C700.2, C701.1, U700.H1 (VREFDQ), U700.M8 (VREFCA)
unnamed: C724.1, C725.1, C726.1, C727.1, C728.1, C729.1, C730.1, C731.1, C732.1, C733.1, U701.B2 (VDD1), U701.D9 (VDD2), U701.G7 (VDD3), U701.K2 (VDD4), U701.K8 (VDD5), U701.N1 (VDD6), U701.N9 (VDD7), U701.R1 (VDD8), U701.R9 (VDD9)
unnamed: C734.1, C735.1, C736.1, C737.1, C738.1, C739.1, C740.1, C741.1, C742.1, C743.1, U701.A1 (VDDQ1), U701.A8 (VDDQ2), U701.C1 (VDDQ3), U701.C9 (VDDQ4), U701.D2 (VDDQ5), U701.E9 (VDDQ6), U701.F1 (VDDQ7), U701.H2 (VDDQ8), U701.H9 (VDDQ9)
unnamed: C722.2, C723.1, U701.H1 (VREFDQ), U701.M8 (VREFCA)
unnamed: C803.1, U800.21 (DVDD10)
unnamed: C800.1, C801.1, U800.29 (DVDD33)
unnamed: C802.1, C814.1, C815.1, FB800.2, U800.28 (DVDD_RG)
unnamed: R818.2, R822.2, U800.32 (LED0/CFG_EXT)
unnamed: R819.1, U800.33 (LED1/CFG_LDO0)
unnamed: R820.2, R823.2, U800.34 (LED2/CFG_LDO1)
unnamed: C901.1, U900.20 (VDD33), U900.21 (VBAT)
unnamed: C902.1, C903.1, C904.1, U900.28 (VDD18), U900.30 (VDD18), U900.32 (VDDIO)
unnamed: C907.1, U901.6 (VIN)
unnamed: C318.1, X300.1 (EN), X300.4 (VDD)
unnamed: C406.1, X400.1 (EN), X400.4 (VDD)
unnamed: C811.1, Y800.1 (EN), Y800.4 (VDD)
unnamed: C900.1, Y900.1 (EN), Y900.4 (VDD)
PG 3V3: J1001.16, J1001.40, U400.2
PL B34 L4 N: J1001.63, U200.W13 (IO_L4N_T0_34)
PL B34 L4 P: J1001.65, U200.V12 (IO_L4P_T0_34)
PL B34 L7 N: J1001.51, U200.Y17 (IO_L7N_T1_34)
PL B34 L7 P: J1001.53, U200.Y16 (IO_L7P_T1_34)
PL B34 L8 N: J1001.69, U200.Y14 (IO_L8N_T1_34)
PL B34 L8 P: J1001.71, U200.W14 (IO_L8P_T1_34)
PL B34 L10 N: J1001.45, U200.W15 (IO_L10N_T1_34)
PL B34 L10 P: J1001.47, U200.V15 (IO_L10P_T1_34)
PL B34 L11 N: J1001.75, U200.U15 (IO_L11N_T1_SRCC_34)
PL B34 L11 P: J1001.77, U200.U14 (IO_L11P_T1_SRCC_34)
PL B34 L14 N: J1001.15, J1001.17, U200.N20 (IO_L14P_T2_SRCC_34), U200.P20 (IO_L14N_T2_SRCC_34)
PL B34 L15 N: J1001.27, U200.U20 (IO_L15N_T2_DQS_34)
PL B34 L15 P: J1001.29, U200.T20 (IO_L15P_T2_DQS_34)
PL B34 L16 N: J1000.51, J1001.21, U200.W20 (IO_L16N_T2_34)
PL B34 L16 P: J1001.23, U200.V20 (IO_L16P_T2_34)
PL B34 L17 N: J1001.33, U200.Y19 (IO_L17N_T2_34)
PL B34 L17 P: J1001.35, U200.Y18 (IO_L17P_T2_34)
PL B34 L18 N: J1001.57, U200.W16 (IO_L18N_T2_34)
PL B34 L18 P: J1001.59, U200.V16 (IO_L18P_T2_34)
PL B35 L3 N: J1000.57, U200.D18 (IO_L3N_T0_DQS_AD1N_35)
PL B35 L3 P: J1000.54, J1000.59, U200.E17 (IO_L3P_T0_DQS_AD1P_35), U200.E18 (IO_L5P_T0_AD9P_35)
PL B35 L5 N: J1000.52, U200.E19 (IO_L5N_T0_AD9N_35)
PL B35 L6 N: J1000.58, U200.F17 (IO_L6N_T0_VREF_35)
PL B35 L6 P: J1000.60, U200.F16 (IO_L6P_T0_35)
PL B35 L7 N: J1000.29, U200.M20 (IO_L7N_T1_AD2N_35)
PL B35 L7 P: J1000.27, U200.M19 (IO_L7P_T1_AD2P_35)
PL B35 L8 N: J1000.36, U200.M18 (IO_L8N_T1_AD10N_35)
PL B35 L8 P: J1000.34, U200.M17 (IO_L8P_T1_AD10P_35)
PL B35 L9 N: J1000.35, U200.L20 (IO_L9N_T1_DQS_AD3N_35)
PL B35 L9 P: J1000.33, U200.L19 (IO_L9P_T1_DQS_AD3P_35)
PL B35 L11 N: J1000.41, U200.L17 (IO_L11N_T1_SRCC_35)
PL B35 L13 N: J1000.48, U200.H17 (IO_L13N_T2_MRCC_35)
PL B35 L13 P: J1000.46, U200.H16 (IO_L13P_T2_MRCC_35)
PL B35 L14 N: J1000.47, U200.H18 (IO_L14N_T2_AD4N_SRCC_35)
PL B35 L14 P: J1000.45, U200.J18 (IO_L14P_T2_AD4P_SRCC_35)
PL B35 L20 N: J1000.64, U200.J14 (IO_L20N_T3_AD6N_35)
PL B35 L20 P: J1000.66, U200.K14 (IO_L20P_T3_AD6P_35)
PL B35 L22 N: J1000.28, U200.N16 (IO_L21N_T3_DQS_AD14N_35)
PL B35 L22 P: J1000.30, U200.L14 (IO_L22P_T3_AD7P_35)
PL B35 L23 N: J1000.24, U200.M15 (IO_L23N_T3_35)
PL B35 L23 P: J1000.22, U200.M14 (IO_L23P_T3_35)
PS CLK 33M33: R420.2, U200.E7 (PS_CLK_500)
PS LED: R413.1, R414.1, U200.E6 (PS_MIO0_500)
PS NPOR: C402.1, R333.2, R403.2, U200.C7 (PS_POR_B_500), U400.4
PS NRST: C401.1, R402.2, R428.1, SW400.3, SW400.4, U200.B10 (PS_SRST_B_501)
PWR EN: J1001.18, J1001.42
QSPI CLK: R419.1, U200.A5 (PS_MIO6_500)
QSPI DQ0 M3: R316.1, U200.B8 (PS_MIO2_500), U404.5 (DI(IO0))
QSPI DQ1 M1: R312.2, U200.D6 (PS_MIO3_500), U404.2 (DI(IO1))
QSPI DQ2 M2: R314.1, U200.B7 (PS_MIO4_500), U404.3 (WP(IO2))
QSPI DQ3 M0: R310.2, U200.A6 (PS_MIO5_500), U404.7 (RESET(IO3))
QSPI NSC: R418.1, U200.A7 (PS_MIO1_500), U404.1 (CS)
SD CLK: R427.1, U200.D9 (PS_MIO12_500)
SD CMD: U200.C6 (PS_MIO11_500), U403.M5 (CMD)
SD D0: R421.2, U200.E9 (PS_MIO10_500), U403.A3 (DAT0)
SD D1: R422.2, U200.E8 (PS_MIO13_500), U403.A4 (DAT1)
SD D2: R423.2, U200.C5 (PS_MIO53_501), U403.A5 (DAT2)
SD D3: R424.2, U200.C8 (PS_MIO51_501), U403.B2 (DAT3)
TCK: R307.1, R329.2, U200.F9 (TCK_0)
TDI: R300.2, R305.1, R330.2, U200.G6 (TDI_0)
TDO: R306.1, R331.2, U200.F6 (TDO_0)
TMS: R301.2, R308.1, R332.2, U200.J6 (TMS_0)
UART TX VCFG1: R405.1, U200.D5 (PS_MIO8_500)
USB CLK: U200.A11 (PS_MIO50_501), U900.1 (CLKOUT)
USB DATA0: U200.E16 (PS_MIO20_501), U900.3 (DATA0)
USB DATA1: U200.A14 (PS_MIO18_501), U900.4 (DATA1)
USB DATA2: U200.D15 (PS_MIO16_501), U900.5 (DATA2)
USB DATA3: U200.A12 (PS_MIO14_500), U900.6 (DATA3)
USB DATA4: U200.F12 (PS_MIO52_501), U900.7 (DATA4)
USB DATA5: U200.A10 (PS_MIO48_501), U900.9 (DATA5)
USB DATA6: U200.E13 (PS_MIO46_501), U900.10 (DATA6)
USB DATA7: U200.C18 (PS_MIO44_501), U900.13 (DATA7)
USB DIR: U200.C16 (PS_MIO26_501), U900.31 (DIR)
USB NRST: R900.2, U200.D14 (PS_MIO42_501), U900.27 (~RESETB)
USB NXT: U200.C15 (PS_MIO22_501), U900.2 (NXT)
USB PHY CPEN: R904.1, U900.17 (CPEN), U901.4 (ENABLE)
USB STP: U200.C13 (PS_MIO24_501), U900.29 (STP)
VCFG0: R404.1, U200.D8 (PS_MIO7_500)
